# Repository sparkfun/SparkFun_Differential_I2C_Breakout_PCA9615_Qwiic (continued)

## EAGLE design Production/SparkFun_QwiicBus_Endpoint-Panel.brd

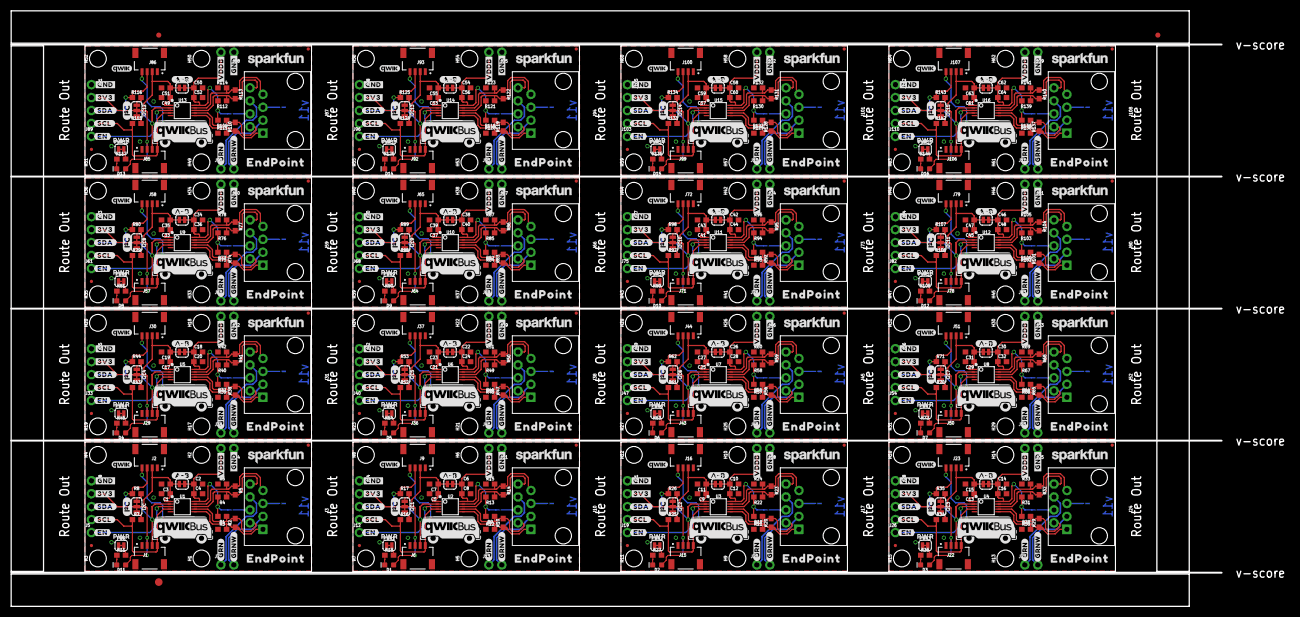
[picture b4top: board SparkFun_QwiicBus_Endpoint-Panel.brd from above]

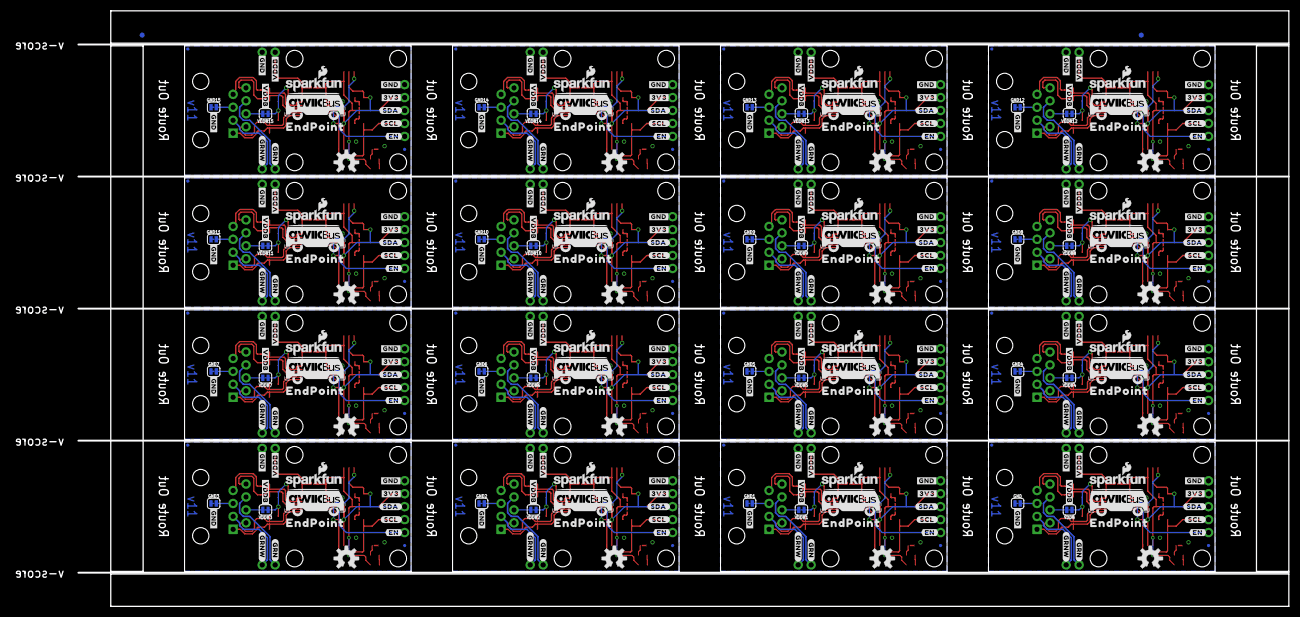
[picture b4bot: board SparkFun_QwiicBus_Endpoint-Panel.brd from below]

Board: 2 copper layers, 237.5 x 116.8 mm, 1077 parts (306 on the bottom side), 288 nets.

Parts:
A-B, A-B1, A-B2, A-B3, A-B4, A-B5, A-B6, A-B7, A-B8, A-B9, A-B10, A-B11, A-B12, A-B13, A-B14, A-B15: JUMPER; SMT-JUMPER_2_NC_TRACE_SILK
C1, C2, C5, C6, C9, C10, C13, C14, C17, C18, C21, C22, C25, C26, C29, C30, C33, C34, C37, C38, C41, C42, C45, C46, C49, C50, C53, C54, C57, C58, C61, C62: 0.1uF; 0603
C3, C4, C7, C8, C11, C12, C15, C16, C19, C20, C23, C24, C27, C28, C31, C32, C35, C36, C39, C40, C43, C44, C47, C48, C51, C52, C55, C56, C59, C60, C63, C64: 1.0uF; 0603
D1, D2, D3, D4, D5, D6, D7, D8, D9, D10, D11, D12, D13, D14, D15, D16: RED; LED-0603
E$1, E$2, E$3, E$4: FIDUCIAL-1X2
E$5: FIDUCIAL-1.5X3
FD1, FD2, FD3, FD4, FD5, FD6, FD7, FD8, FD9, FD10, FD11, FD12, FD13, FD14, FD15, FD16, FD17, FD18, FD19, FD20, FD21, FD22, FD23, FD24, FD25, FD26, FD27, FD28, FD29, FD30, FD31, FD32, FD33, FD34, FD35, FD36, FD37, FD38, FD39, FD40, FD41, FD42, FD43, FD44, FD45, FD46, FD47, FD48, FD49, FD50, FD51, FD52, FD53, FD54, FD55, FD56, FD57, FD58, FD59, FD60, FD61, FD62, FD63, FD64: FIDUCIALUFIDUCIAL; FIDUCIAL-MICRO
GND, GND1, GND2, GND3, GND4, GND5, GND6, GND7, GND8, GND9, GND10, GND11, GND12, GND13, GND14, GND15: JUMPER-SMT_2_NC_TRACE_SILK; SMT-JUMPER_2_NC_TRACE_SILK
H1, H2, H3, H4, H5, H6, H7, H8, H9, H10, H11, H12, H13, H14, H15, H16, H17, H18, H19, H20, H21, H22, H23, H24, H25, H26, H27, H28, H29, H30, H31, H32, H33, H34, H35, H36, H37, H38, H39, H40, H41, H42, H43, H44, H45, H46, H47, H48, H49, H50, H51, H52, H53, H54, H55, H56, H57, H58, H59, H60, H61, H62, H63, H64: STAND-OFF
I2C, I2C1, I2C2, I2C3, I2C4, I2C5, I2C6, I2C7, I2C8, I2C9, I2C10, I2C11, I2C12, I2C13, I2C14, I2C15: JUMPER-SMT_3_2-NC_TRACE_SILK; SMT-JUMPER_3_2-NC_TRACE_SILK
J1, J2, J6, J9, J15, J16, J22, J23, J29, J30, J36, J37, J43, J44, J50, J51, J57, J58, J64, J65, J71, J72, J78, J79, J85, J86, J92, J93, J99, J100, J106, J107: QWIIC; JST04_1MM_RA
J3, J10, J17, J24, J31, J38, J45, J52, J59, J66, J73, J80, J87, J94, J101, J108: RJ45; RJ45-8
J4, J7, J11, J13, J18, J20, J25, J27, J32, J34, J39, J41, J46, J48, J53, J55, J60, J62, J67, J69, J74, J76, J81, J83, J88, J90, J95, J97, J102, J104, J109, J111: 1X02_NO_SILK
J5, J12, J19, J26, J33, J40, J47, J54, J61, J68, J75, J82, J89, J96, J103, J110: 1X01_NO_SILK
J8, J14, J21, J28, J35, J42, J49, J56, J63, J70, J77, J84, J91, J98, J105, J112: 1X04_NO_SILK
LOGO1, LOGO6, LOGO11, LOGO16, LOGO21, LOGO26, LOGO31, LOGO36, LOGO41, LOGO46, LOGO51, LOGO56, LOGO61, LOGO66, LOGO71, LOGO76: OSHW-LOGOM; OSHW-LOGO-M
LOGO2, LOGO8, LOGO13, LOGO18, LOGO23, LOGO28, LOGO33, LOGO38, LOGO43, LOGO48, LOGO53, LOGO58, LOGO63, LOGO68, LOGO73, LOGO78: REVISION
LOGO3, LOGO9, LOGO14, LOGO19, LOGO24, LOGO29, LOGO34, LOGO39, LOGO44, LOGO49, LOGO54, LOGO59, LOGO64, LOGO69, LOGO74, LOGO79: QWIIC_LOGO_4MM; QWIIC_4MM
LOGO4, LOGO10, LOGO15, LOGO20, LOGO25, LOGO30, LOGO35, LOGO40, LOGO45, LOGO50, LOGO55, LOGO60, LOGO65, LOGO70, LOGO75, LOGO80: SFE_LOGO_NAME_FLAME.1_INCH; SFE_LOGO_NAME_FLAME_.1
LOGO5, LOGO7, LOGO12, LOGO17, LOGO22, LOGO27, LOGO32, LOGO37, LOGO42, LOGO47, LOGO52, LOGO57, LOGO62, LOGO67, LOGO72, LOGO77: SFE_LOGO_NAME.1_INCH; SFE_LOGO_NAME_.1
PWR, PWR1, PWR2, PWR3, PWR4, PWR5, PWR6, PWR7, PWR8, PWR9, PWR10, PWR11, PWR12, PWR13, PWR14, PWR15: JUMPER-SMT_2_NC_TRACE_SILK; SMT-JUMPER_2_NC_TRACE_SILK
R1, R3, R4, R6, R9, R12, R13, R15, R19, R21, R22, R24, R28, R30, R31, R33, R37, R39, R40, R42, R46, R48, R49, R51, R55, R57, R58, R60, R64, R66, R67, R69, R73, R75, R76, R78, R82, R84, R85, R87, R91, R93, R94, R96, R100, R102, R103, R105, R109, R111, R112, R114, R118, R120, R121, R123, R127, R129, R130, R132, R136, R138, R139, R141: 390; 0603
R2, R5, R10, R14, R20, R23, R29, R32, R38, R41, R47, R50, R56, R59, R65, R68, R74, R77, R83, R86, R92, R95, R101, R104, R110, R113, R119, R122, R128, R131, R137, R140: 100; 0603
R7, R8, R16, R17, R25, R26, R34, R35, R43, R44, R52, R53, R61, R62, R70, R71, R79, R80, R88, R89, R97, R98, R106, R107, R115, R116, R124, R125, R133, R134, R142, R143: 4.7k; 0603
R11, R18, R27, R36, R45, R54, R63, R72, R81, R90, R99, R108, R117, R126, R135, R144: 1k; 0603
U1, U2, U3, U4, U5, U6, U7, U8, U9, U10, U11, U12, U13, U14, U15, U16: PCA9615; TSSOP10
U$1, U$24, U$55, U$82, U$109, U$136, U$163, U$190, U$217, U$244, U$271, U$298, U$325, U$352, U$379, U$406: I2C
U$2, U$3, U$4, U$5, U$6, U$29, U$30, U$31, U$32, U$33, U$56, U$57, U$58, U$59, U$60, U$83, U$84, U$85, U$86, U$87, U$110, U$111, U$112, U$113, U$114, U$137, U$138, U$139, U$140, U$141, U$164, U$165, U$166, U$167, U$168, U$191, U$192, U$193, U$194, U$195, U$218, U$219, U$220, U$221, U$222, U$245, U$246, U$247, U$248, U$249, U$272, U$273, U$274, U$275, U$276, U$299, U$300, U$301, U$302, U$303, U$326, U$327, U$328, U$329, U$330, U$353, U$354, U$355, U$356, U$357, U$380, U$381, U$382, U$383, U$384, U$407, U$408, U$409, U$410, U$411: #GND#0
U$7, U$8, U$34, U$35, U$61, U$62, U$88, U$89, U$115, U$116, U$142, U$143, U$169, U$170, U$196, U$197, U$223, U$224, U$250, U$251, U$277, U$278, U$304, U$305, U$331, U$332, U$358, U$359, U$385, U$386, U$412, U$413: #3V3#0
U$9, U$15, U$36, U$42, U$63, U$69, U$90, U$96, U$117, U$123, U$144, U$150, U$171, U$177, U$198, U$204, U$225, U$231, U$252, U$258, U$279, U$285, U$306, U$312, U$333, U$339, U$360, U$366, U$387, U$393, U$414, U$420: #SDA#0
U$10, U$16, U$37, U$43, U$64, U$70, U$91, U$97, U$118, U$124, U$145, U$151, U$172, U$178, U$199, U$205, U$226, U$232, U$253, U$259, U$280, U$286, U$307, U$313, U$334, U$340, U$361, U$367, U$388, U$394, U$415, U$421: #SCL#0
U$11, U$17, U$38, U$44, U$65, U$71, U$92, U$98, U$119, U$125, U$146, U$152, U$173, U$179, U$200, U$206, U$227, U$233, U$254, U$260, U$281, U$287, U$308, U$314, U$335, U$341, U$362, U$368, U$389, U$395, U$416, U$422: #EN#0
U$12, U$13, U$14, U$39, U$40, U$41, U$66, U$67, U$68, U$93, U$94, U$95, U$120, U$121, U$122, U$147, U$148, U$149, U$174, U$175, U$176, U$201, U$202, U$203, U$228, U$229, U$230, U$255, U$256, U$257, U$282, U$283, U$284, U$309, U$310, U$311, U$336, U$337, U$338, U$363, U$364, U$365, U$390, U$391, U$392, U$417, U$418, U$419: #VDDB#0
U$18, U$45, U$72, U$99, U$126, U$153, U$180, U$207, U$234, U$261, U$288, U$315, U$342, U$369, U$396, U$423: #A#B#0
U$19, U$20, U$46, U$47, U$73, U$74, U$100, U$101, U$127, U$128, U$154, U$155, U$181, U$182, U$208, U$209, U$235, U$236, U$262, U$263, U$289, U$290, U$316, U$317, U$343, U$344, U$370, U$371, U$397, U$398, U$424, U$425: #GRNW#0
U$21, U$22, U$48, U$49, U$75, U$76, U$102, U$103, U$129, U$130, U$156, U$157, U$183, U$184, U$210, U$211, U$237, U$238, U$264, U$265, U$291, U$292, U$318, U$319, U$345, U$346, U$372, U$373, U$399, U$400, U$426, U$427: #GRN#0
U$23, U$28, U$53, U$54, U$80, U$81, U$107, U$108, U$134, U$135, U$161, U$162, U$188, U$189, U$215, U$216, U$242, U$243, U$269, U$270, U$296, U$297, U$323, U$324, U$350, U$351, U$377, U$378, U$404, U$405, U$431, U$432: QWIICBUS#WORKING#LOGO#JPG
U$25, U$26, U$50, U$51, U$77, U$78, U$104, U$105, U$131, U$132, U$158, U$159, U$185, U$186, U$212, U$213, U$239, U$240, U$266, U$267, U$293, U$294, U$320, U$321, U$347, U$348, U$374, U$375, U$401, U$402, U$428, U$429: ENDPOINT0
U$27, U$52, U$79, U$106, U$133, U$160, U$187, U$214, U$241, U$268, U$295, U$322, U$349, U$376, U$403, U$430: PWR0
VDDB, VDDB1, VDDB2, VDDB3, VDDB4, VDDB5, VDDB6, VDDB7, VDDB8, VDDB9, VDDB10, VDDB11, VDDB12, VDDB13, VDDB14, VDDB15: JUMPER-SMT_2_NC_TRACE_SILK; SMT-JUMPER_2_NC_TRACE_SILK

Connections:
DSCL_N: J3.1, R2.1, R3.2, U1.6
DSCL_N1: J10.1, R10.1, R12.2, U2.6
DSCL_N2: J17.1, R20.1, R21.2, U3.6
DSCL_N3: J24.1, R29.1, R30.2, U4.6
DSCL_N4: J31.1, R38.1, R39.2, U5.6
DSCL_N5: J38.1, R47.1, R48.2, U6.6
DSCL_N6: J45.1, R56.1, R57.2, U7.6
DSCL_N7: J52.1, R65.1, R66.2, U8.6
DSCL_N8: J59.1, R74.1, R75.2, U9.6
DSCL_N9: J66.1, R83.1, R84.2, U10.6
DSCL_N10: J73.1, R92.1, R93.2, U11.6
DSCL_N11: J80.1, R101.1, R102.2, U12.6
DSCL_N12: J87.1, R110.1, R111.2, U13.6
DSCL_N13: J94.1, R119.1, R120.2, U14.6
DSCL_N14: J101.1, R128.1, R129.2, U15.6
DSCL_N15: J108.1, R137.1, R138.2, U16.6
DSCL_P: J3.2, R1.1, R2.2, U1.7
DSCL_P1: J10.2, R9.1, R10.2, U2.7
DSCL_P2: J17.2, R19.1, R20.2, U3.7
DSCL_P3: J24.2, R28.1, R29.2, U4.7
DSCL_P4: J31.2, R37.1, R38.2, U5.7
DSCL_P5: J38.2, R46.1, R47.2, U6.7
DSCL_P6: J45.2, R55.1, R56.2, U7.7
DSCL_P7: J52.2, R64.1, R65.2, U8.7
DSCL_P8: J59.2, R73.1, R74.2, U9.7
DSCL_P9: J66.2, R82.1, R83.2, U10.7
DSCL_P10: J73.2, R91.1, R92.2, U11.7
DSCL_P11: J80.2, R100.1, R101.2, U12.7
DSCL_P12: J87.2, R109.1, R110.2, U13.7
DSCL_P13: J94.2, R118.1, R119.2, U14.7
DSCL_P14: J101.2, R127.1, R128.2, U15.7
DSCL_P15: J108.2, R136.1, R137.2, U16.7
DSDA_N: J3.7, R5.1, R6.2, U1.9
DSDA_N1: J10.7, R14.1, R15.2, U2.9
DSDA_N2: J17.7, R23.1, R24.2, U3.9
DSDA_N3: J24.7, R32.1, R33.2, U4.9
DSDA_N4: J31.7, R41.1, R42.2, U5.9
DSDA_N5: J38.7, R50.1, R51.2, U6.9
DSDA_N6: J45.7, R59.1, R60.2, U7.9
DSDA_N7: J52.7, R68.1, R69.2, U8.9
DSDA_N8: J59.7, R77.1, R78.2, U9.9
DSDA_N9: J66.7, R86.1, R87.2, U10.9
DSDA_N10: J73.7, R95.1, R96.2, U11.9
DSDA_N11: J80.7, R104.1, R105.2, U12.9
DSDA_N12: J87.7, R113.1, R114.2, U13.9
DSDA_N13: J94.7, R122.1, R123.2, U14.9
DSDA_N14: J101.7, R131.1, R132.2, U15.9
DSDA_N15: J108.7, R140.1, R141.2, U16.9
DSDA_P: J3.8, R4.1, R5.2, U1.8
DSDA_P1: J10.8, R13.1, R14.2, U2.8
DSDA_P2: J17.8, R22.1, R23.2, U3.8
DSDA_P3: J24.8, R31.1, R32.2, U4.8
DSDA_P4: J31.8, R40.1, R41.2, U5.8
DSDA_P5: J38.8, R49.1, R50.2, U6.8
DSDA_P6: J45.8, R58.1, R59.2, U7.8
DSDA_P7: J52.8, R67.1, R68.2, U8.8
DSDA_P8: J59.8, R76.1, R77.2, U9.8
DSDA_P9: J66.8, R85.1, R86.2, U10.8
DSDA_P10: J73.8, R94.1, R95.2, U11.8
DSDA_P11: J80.8, R103.1, R104.2, U12.8
DSDA_P12: J87.8, R112.1, R113.2, U13.8
DSDA_P13: J94.8, R121.1, R122.2, U14.8
DSDA_P14: J101.8, R130.1, R131.2, U15.8
DSDA_P15: J108.8, R139.1, R140.2, U16.8
EN: J5.1, U1.3
EN1: J12.1, U2.3
EN2: J19.1, U3.3
EN3: J26.1, U4.3
EN4: J33.1, U5.3
EN5: J40.1, U6.3
EN6: J47.1, U7.3
EN7: J54.1, U8.3
EN8: J61.1, U9.3
EN9: J68.1, U10.3
EN10: J75.1, U11.3
EN11: J82.1, U12.3
EN12: J89.1, U13.3
EN13: J96.1, U14.3
EN14: J103.1, U15.3
EN15: J110.1, U16.3
GND: C1.2, C2.2, C3.2, C4.2, GND.1, J1.1, J2.1, J4.1, J8.1, PWR.1, R3.1, R6.1, U1.5
GND1: C5.2, C6.2, C7.2, C8.2, GND1.1, J6.1, J9.1, J11.1, J14.1, PWR1.1, R12.1, R15.1, U2.5
GND2: C9.2, C10.2, C11.2, C12.2, GND2.1, J15.1, J16.1, J18.1, J21.1, PWR2.1, R21.1, R24.1, U3.5
GND3: C13.2, C14.2, C15.2, C16.2, GND3.1, J22.1, J23.1, J25.1, J28.1, PWR3.1, R30.1, R33.1, U4.5
GND4: C17.2, C18.2, C19.2, C20.2, GND4.1, J29.1, J30.1, J32.1, J35.1, PWR4.1, R39.1, R42.1, U5.5
GND5: C21.2, C22.2, C23.2, C24.2, GND5.1, J36.1, J37.1, J39.1, J42.1, PWR5.1, R48.1, R51.1, U6.5
GND6: C25.2, C26.2, C27.2, C28.2, GND6.1, J43.1, J44.1, J46.1, J49.1, PWR6.1, R57.1, R60.1, U7.5
GND7: C29.2, C30.2, C31.2, C32.2, GND7.1, J50.1, J51.1, J53.1, J56.1, PWR7.1, R66.1, R69.1, U8.5
GND8: C33.2, C34.2, C35.2, C36.2, GND8.1, J57.1, J58.1, J60.1, J63.1, PWR8.1, R75.1, R78.1, U9.5
GND9: C37.2, C38.2, C39.2, C40.2, GND9.1, J64.1, J65.1, J67.1, J70.1, PWR9.1, R84.1, R87.1, U10.5
GND10: C41.2, C42.2, C43.2, C44.2, GND10.1, J71.1, J72.1, J74.1, J77.1, PWR10.1, R93.1, R96.1, U11.5
GND11: C45.2, C46.2, C47.2, C48.2, GND11.1, J78.1, J79.1, J81.1, J84.1, PWR11.1, R102.1, R105.1, U12.5
GND12: C49.2, C50.2, C51.2, C52.2, GND12.1, J85.1, J86.1, J88.1, J91.1, PWR12.1, R111.1, R114.1, U13.5
GND13: C53.2, C54.2, C55.2, C56.2, GND13.1, J92.1, J93.1, J95.1, J98.1, PWR13.1, R120.1, R123.1, U14.5
GND14: C57.2, C58.2, C59.2, C60.2, GND14.1, J99.1, J100.1, J102.1, J105.1, PWR14.1, R129.1, R132.1, U15.5
GND15: C61.2, C62.2, C63.2, C64.2, GND15.1, J106.1, J107.1, J109.1, J112.1, PWR15.1, R138.1, R141.1, U16.5
GRN_N: J3.6, J7.1
GRN_N1: J10.6, J13.1
GRN_N2: J17.6, J20.1
GRN_N3: J24.6, J27.1
GRN_N4: J31.6, J34.1
GRN_N5: J38.6, J41.1
GRN_N6: J45.6, J48.1
GRN_N7: J52.6, J55.1
GRN_N8: J59.6, J62.1
GRN_N9: J66.6, J69.1
GRN_N10: J73.6, J76.1
GRN_N11: J80.6, J83.1
GRN_N12: J87.6, J90.1
GRN_N13: J94.6, J97.1
GRN_N14: J101.6, J104.1
GRN_N15: J108.6, J111.1
GRN_P: J3.3, J7.2
GRN_P1: J10.3, J13.2
GRN_P2: J17.3, J20.2
GRN_P3: J24.3, J27.2
GRN_P4: J31.3, J34.2
GRN_P5: J38.3, J41.2
GRN_P6: J45.3, J48.2
GRN_P7: J52.3, J55.2
GRN_P8: J59.3, J62.2
GRN_P9: J66.3, J69.2
GRN_P10: J73.3, J76.2
GRN_P11: J80.3, J83.2
GRN_P12: J87.3, J90.2
GRN_P13: J94.3, J97.2
GRN_P14: J101.3, J104.2
GRN_P15: J108.3, J111.2
unnamed: J3.4, VDDB.2
unnamed: GND.2, J3.5
unnamed: I2C.1, R8.2
unnamed: I2C.3, R7.2
unnamed: I2C1.1, R17.2
unnamed: I2C1.3, R16.2
unnamed: J10.4, VDDB1.2
unnamed: GND1.2, J10.5
unnamed: D1.C, R18.1
unnamed: PWR1.2, R18.2
unnamed: I2C2.1, R26.2
unnamed: I2C2.3, R25.2
unnamed: D11.C, R11.1
unnamed: PWR.2, R11.2
unnamed: J17.4, VDDB2.2
unnamed: GND2.2, J17.5
unnamed: D2.C, R27.1
unnamed: PWR2.2, R27.2
unnamed: I2C3.1, R35.2
unnamed: I2C3.3, R34.2
unnamed: J24.4, VDDB3.2
unnamed: GND3.2, J24.5
unnamed: D3.C, R36.1
unnamed: PWR3.2, R36.2
unnamed: I2C4.1, R44.2
unnamed: I2C4.3, R43.2
unnamed: J31.4, VDDB4.2
unnamed: GND4.2, J31.5
unnamed: D4.C, R45.1
unnamed: PWR4.2, R45.2
unnamed: I2C5.1, R53.2
unnamed: I2C5.3, R52.2
unnamed: J38.4, VDDB5.2
unnamed: GND5.2, J38.5
unnamed: D5.C, R54.1
unnamed: PWR5.2, R54.2
unnamed: I2C6.1, R62.2
unnamed: I2C6.3, R61.2
unnamed: J45.4, VDDB6.2
unnamed: GND6.2, J45.5
unnamed: D6.C, R63.1
unnamed: PWR6.2, R63.2
unnamed: I2C7.1, R71.2
unnamed: I2C7.3, R70.2
unnamed: J52.4, VDDB7.2
unnamed: GND7.2, J52.5
unnamed: D7.C, R72.1
unnamed: PWR7.2, R72.2
unnamed: I2C8.1, R80.2
unnamed: I2C8.3, R79.2
unnamed: J59.4, VDDB8.2
unnamed: GND8.2, J59.5
unnamed: D8.C, R81.1
unnamed: PWR8.2, R81.2
unnamed: I2C9.1, R89.2
unnamed: I2C9.3, R88.2
unnamed: J66.4, VDDB9.2
unnamed: GND9.2, J66.5
unnamed: D9.C, R90.1
unnamed: PWR9.2, R90.2
unnamed: I2C10.1, R98.2
unnamed: I2C10.3, R97.2
unnamed: J73.4, VDDB10.2
unnamed: GND10.2, J73.5
unnamed: D10.C, R99.1
unnamed: PWR10.2, R99.2
unnamed: I2C11.1, R107.2
unnamed: I2C11.3, R106.2
unnamed: J80.4, VDDB11.2
unnamed: GND11.2, J80.5
unnamed: D12.C, R108.1
unnamed: PWR11.2, R108.2
unnamed: I2C12.1, R116.2
unnamed: I2C12.3, R115.2
unnamed: J87.4, VDDB12.2
unnamed: GND12.2, J87.5
unnamed: D13.C, R117.1
unnamed: PWR12.2, R117.2
unnamed: I2C13.1, R125.2
unnamed: I2C13.3, R124.2
unnamed: J94.4, VDDB13.2
unnamed: GND13.2, J94.5
unnamed: D14.C, R126.1
unnamed: PWR13.2, R126.2
unnamed: I2C14.1, R134.2
unnamed: I2C14.3, R133.2
unnamed: J101.4, VDDB14.2
unnamed: GND14.2, J101.5
unnamed: D15.C, R135.1
unnamed: PWR14.2, R135.2
unnamed: I2C15.1, R143.2
unnamed: I2C15.3, R142.2
unnamed: J108.4, VDDB15.2
unnamed: GND15.2, J108.5
unnamed: D16.C, R144.1
unnamed: PWR15.2, R144.2
SCL: J1.4, J2.4, J8.4, R7.1, U1.4
SCL1: J6.4, J9.4, J14.4, R16.1, U2.4
SCL2: J15.4, J16.4, J21.4, R25.1, U3.4
SCL3: J22.4, J23.4, J28.4, R34.1, U4.4
SCL4: J29.4, J30.4, J35.4, R43.1, U5.4
SCL5: J36.4, J37.4, J42.4, R52.1, U6.4
SCL6: J43.4, J44.4, J49.4, R61.1, U7.4
SCL7: J50.4, J51.4, J56.4, R70.1, U8.4
SCL8: J57.4, J58.4, J63.4, R79.1, U9.4
SCL9: J64.4, J65.4, J70.4, R88.1, U10.4
SCL10: J71.4, J72.4, J77.4, R97.1, U11.4
SCL11: J78.4, J79.4, J84.4, R106.1, U12.4
SCL12: J85.4, J86.4, J91.4, R115.1, U13.4
SCL13: J92.4, J93.4, J98.4, R124.1, U14.4
SCL14: J99.4, J100.4, J105.4, R133.1, U15.4
SCL15: J106.4, J107.4, J112.4, R142.1, U16.4
SDA: J1.3, J2.3, J8.3, R8.1, U1.2
SDA1: J6.3, J9.3, J14.3, R17.1, U2.2
SDA2: J15.3, J16.3, J21.3, R26.1, U3.2
SDA3: J22.3, J23.3, J28.3, R35.1, U4.2
SDA4: J29.3, J30.3, J35.3, R44.1, U5.2
SDA5: J36.3, J37.3, J42.3, R53.1, U6.2
SDA6: J43.3, J44.3, J49.3, R62.1, U7.2
SDA7: J50.3, J51.3, J56.3, R71.1, U8.2
SDA8: J57.3, J58.3, J63.3, R80.1, U9.2
SDA9: J64.3, J65.3, J70.3, R89.1, U10.2
SDA10: J71.3, J72.3, J77.3, R98.1, U11.2
SDA11: J78.3, J79.3, J84.3, R107.1, U12.2
SDA12: J85.3, J86.3, J91.3, R116.1, U13.2
SDA13: J92.3, J93.3, J98.3, R125.1, U14.2
SDA14: J99.3, J100.3, J105.3, R134.1, U15.2
SDA15: J106.3, J107.3, J112.3, R143.1, U16.2
VDD_A: A-B.1, C1.1, C3.1, D11.A, I2C.2, J1.2, J2.2, J8.2, U1.1
VDD_A1: A-B1.1, C5.1, C7.1, D1.A, I2C1.2, J6.2, J9.2, J14.2, U2.1
VDD_A2: A-B2.1, C9.1, C11.1, D2.A, I2C2.2, J15.2, J16.2, J21.2, U3.1
VDD_A3: A-B3.1, C13.1, C15.1, D3.A, I2C3.2, J22.2, J23.2, J28.2, U4.1
VDD_A4: A-B4.1, C17.1, C19.1, D4.A, I2C4.2, J29.2, J30.2, J35.2, U5.1
VDD_A5: A-B5.1, C21.1, C23.1, D5.A, I2C5.2, J36.2, J37.2, J42.2, U6.1
VDD_A6: A-B6.1, C25.1, C27.1, D6.A, I2C6.2, J43.2, J44.2, J49.2, U7.1
VDD_A7: A-B7.1, C29.1, C31.1, D7.A, I2C7.2, J50.2, J51.2, J56.2, U8.1
VDD_A8: A-B8.1, C33.1, C35.1, D8.A, I2C8.2, J57.2, J58.2, J63.2, U9.1
VDD_A9: A-B9.1, C37.1, C39.1, D9.A, I2C9.2, J64.2, J65.2, J70.2, U10.1
VDD_A10: A-B10.1, C41.1, C43.1, D10.A, I2C10.2, J71.2, J72.2, J77.2, U11.1
VDD_A11: A-B11.1, C45.1, C47.1, D12.A, I2C11.2, J78.2, J79.2, J84.2, U12.1
VDD_A12: A-B12.1, C49.1, C51.1, D13.A, I2C12.2, J85.2, J86.2, J91.2, U13.1
VDD_A13: A-B13.1, C53.1, C55.1, D14.A, I2C13.2, J92.2, J93.2, J98.2, U14.1
VDD_A14: A-B14.1, C57.1, C59.1, D15.A, I2C14.2, J99.2, J100.2, J105.2, U15.1
VDD_A15: A-B15.1, C61.1, C63.1, D16.A, I2C15.2, J106.2, J107.2, J112.2, U16.1
VDD_B: A-B.2, C2.1, C4.1, J4.2, R1.2, R4.2, U1.10, VDDB.1
VDD_B1: A-B1.2, C6.1, C8.1, J11.2, R9.2, R13.2, U2.10, VDDB1.1
VDD_B2: A-B2.2, C10.1, C12.1, J18.2, R19.2, R22.2, U3.10, VDDB2.1
VDD_B3: A-B3.2, C14.1, C16.1, J25.2, R28.2, R31.2, U4.10, VDDB3.1
VDD_B4: A-B4.2, C18.1, C20.1, J32.2, R37.2, R40.2, U5.10, VDDB4.1
VDD_B5: A-B5.2, C22.1, C24.1, J39.2, R46.2, R49.2, U6.10, VDDB5.1
VDD_B6: A-B6.2, C26.1, C28.1, J46.2, R55.2, R58.2, U7.10, VDDB6.1
VDD_B7: A-B7.2, C30.1, C32.1, J53.2, R64.2, R67.2, U8.10, VDDB7.1
VDD_B8: A-B8.2, C34.1, C36.1, J60.2, R73.2, R76.2, U9.10, VDDB8.1
VDD_B9: A-B9.2, C38.1, C40.1, J67.2, R82.2, R85.2, U10.10, VDDB9.1
VDD_B10: A-B10.2, C42.1, C44.1, J74.2, R91.2, R94.2, U11.10, VDDB10.1
VDD_B11: A-B11.2, C46.1, C48.1, J81.2, R100.2, R103.2, U12.10, VDDB11.1
VDD_B12: A-B12.2, C50.1, C52.1, J88.2, R109.2, R112.2, U13.10, VDDB12.1
VDD_B13: A-B13.2, C54.1, C56.1, J95.2, R118.2, R121.2, U14.10, VDDB13.1
VDD_B14: A-B14.2, C58.1, C60.1, J102.2, R127.2, R130.2, U15.10, VDDB14.1
VDD_B15: A-B15.2, C62.1, C64.1, J109.2, R136.2, R139.2, U16.10, VDDB15.1

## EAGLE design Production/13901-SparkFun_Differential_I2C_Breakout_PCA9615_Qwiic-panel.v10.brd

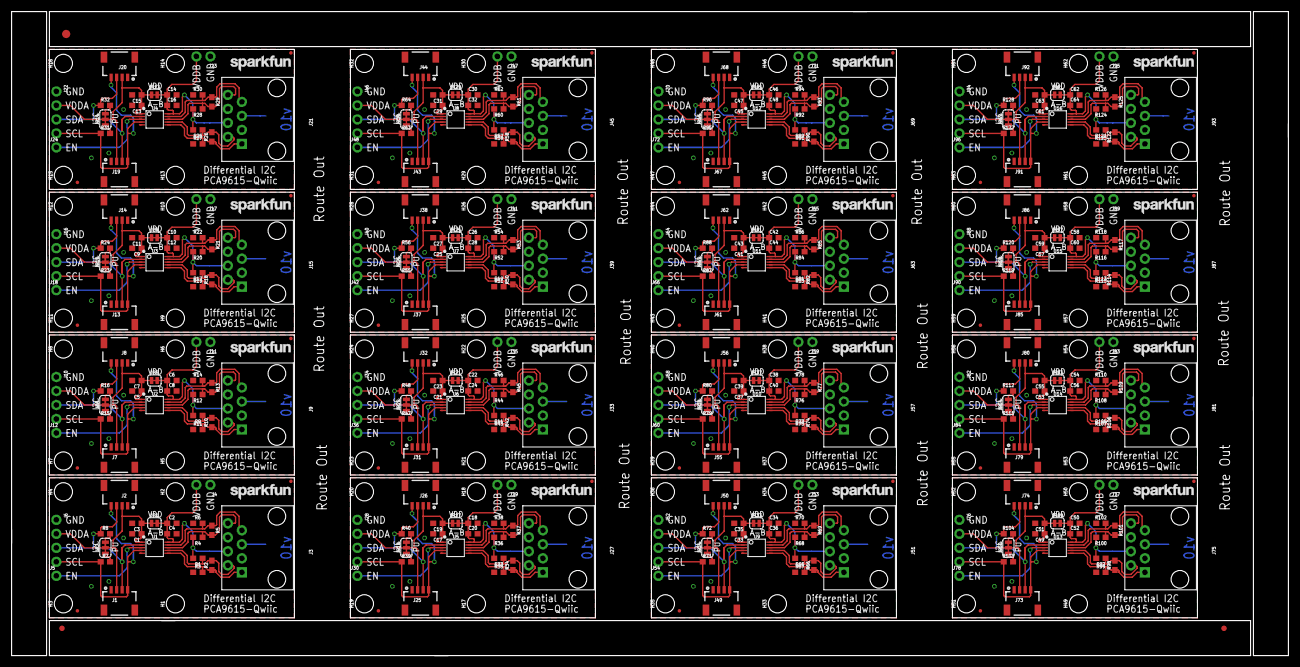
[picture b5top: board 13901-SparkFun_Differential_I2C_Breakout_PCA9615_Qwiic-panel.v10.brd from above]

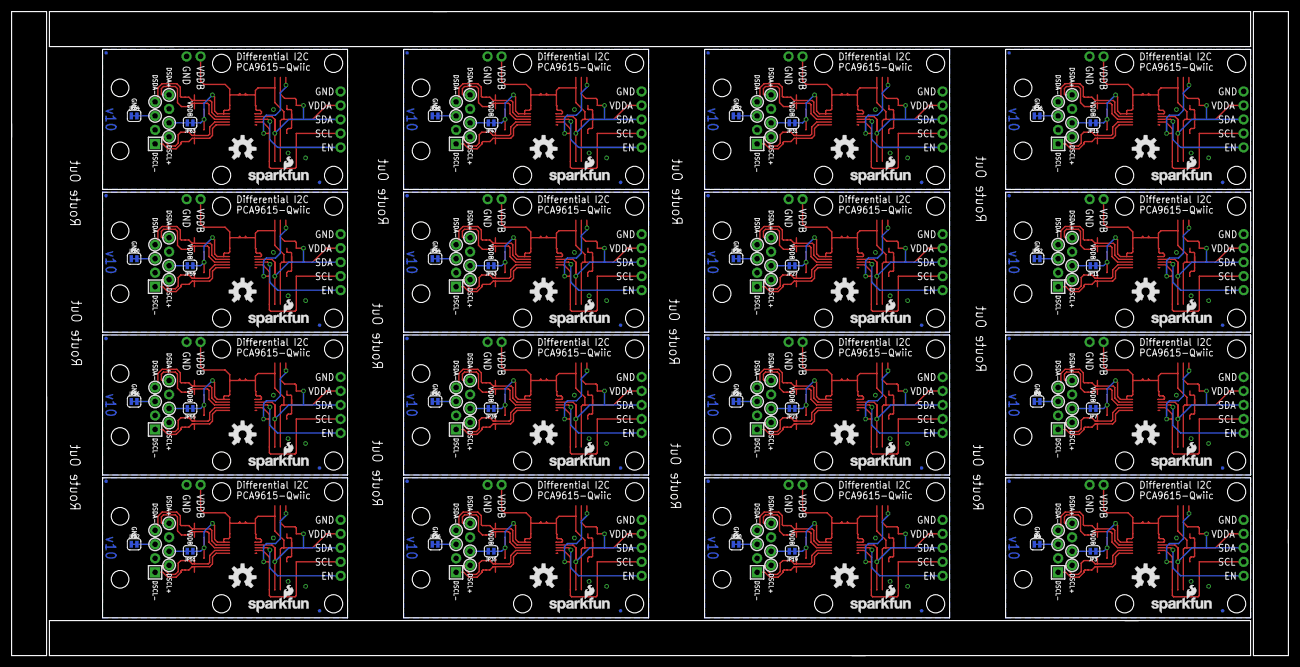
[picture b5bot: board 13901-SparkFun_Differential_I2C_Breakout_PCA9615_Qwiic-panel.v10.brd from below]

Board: 2 copper layers, 231.6 x 116.8 mm, 547 parts (96 on the bottom side), 224 nets.

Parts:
C1, C2, C5, C6, C9, C10, C13, C14, C17, C18, C21, C22, C25, C26, C29, C30, C33, C34, C37, C38, C41, C42, C45, C46, C49, C50, C53, C54, C57, C58, C61, C62: 0.1uF; 0603
C3, C4, C7, C8, C11, C12, C15, C16, C19, C20, C23, C24, C27, C28, C31, C32, C35, C36, C39, C40, C43, C44, C47, C48, C51, C52, C55, C56, C59, C60, C63, C64: 1.0uF; 0603
E$1, E$2: FIDUCIAL-1X2
E$3: FIDUCIAL-1.5X3
FD1, FD2, FD3, FD4, FD5, FD6, FD7, FD8, FD9, FD10, FD11, FD12, FD13, FD14, FD15, FD16, FD17, FD18, FD19, FD20, FD21, FD22, FD23, FD24, FD25, FD26, FD27, FD28, FD29, FD30, FD31, FD32, FD33, FD34, FD35, FD36, FD37, FD38, FD39, FD40, FD41, FD42, FD43, FD44, FD45, FD46, FD47, FD48, FD49, FD50, FD51, FD52, FD53, FD54, FD55, FD56, FD57, FD58, FD59, FD60, FD61, FD62, FD63, FD64: FIDUCIALUFIDUCIAL; FIDUCIAL-MICRO
H1, H2, H3, H4, H5, H6, H7, H8, H9, H10, H11, H12, H13, H14, H15, H16, H17, H18, H19, H20, H21, H22, H23, H24, H25, H26, H27, H28, H29, H30, H31, H32, H33, H34, H35, H36, H37, H38, H39, H40, H41, H42, H43, H44, H45, H46, H47, H48, H49, H50, H51, H52, H53, H54, H55, H56, H57, H58, H59, H60, H61, H62, H63, H64: STAND-OFF
J1, J2, J7, J8, J13, J14, J19, J20, J25, J26, J31, J32, J37, J38, J43, J44, J49, J50, J55, J56, J61, J62, J67, J68, J73, J74, J79, J80, J85, J86, J91, J92: 1X04_1MM_RA
J3, J9, J15, J21, J27, J33, J39, J45, J51, J57, J63, J69, J75, J81, J87, J93: RJ45; RJ45-8
J4, J11, J17, J23, J29, J35, J41, J47, J53, J59, J65, J71, J77, J83, J89, J95: 1X02_NO_SILK
J5, J12, J18, J24, J30, J36, J42, J48, J54, J60, J66, J72, J78, J84, J90, J96: 1X01_NO_SILK
J6, J10, J16, J22, J28, J34, J40, J46, J52, J58, J64, J70, J76, J82, J88, J94: 1X04_NO_SILK
JP1, JP5, JP9, JP13, JP17, JP21, JP25, JP29, JP33, JP37, JP41, JP45, JP49, JP53, JP57, JP61: JUMPER; SMT-JUMPER_2_NC_TRACE_SILK
JP2, JP6, JP10, JP14, JP18, JP22, JP26, JP30, JP34, JP38, JP42, JP46, JP50, JP54, JP58, JP62: SMT-JUMPER_3_2-NC_TRACE_SILK
JP3, JP4, JP7, JP8, JP11, JP12, JP15, JP16, JP19, JP20, JP23, JP24, JP27, JP28, JP31, JP32, JP35, JP36, JP39, JP40, JP43, JP44, JP47, JP48, JP51, JP52, JP55, JP56, JP59, JP60, JP63, JP64: SMT-JUMPER_2_NC_TRACE_SILK
LOGO1, LOGO2, LOGO7, LOGO10, LOGO13, LOGO16, LOGO19, LOGO22, LOGO25, LOGO28, LOGO31, LOGO34, LOGO37, LOGO40, LOGO43, LOGO46: OSHW-LOGOM; OSHW-LOGO-M
LOGO3, LOGO6, LOGO9, LOGO12, LOGO15, LOGO18, LOGO21, LOGO24, LOGO27, LOGO30, LOGO33, LOGO36, LOGO39, LOGO42, LOGO45, LOGO48: SFE_LOGO_NAME.1_INCH; SFE_LOGO_NAME_.1
LOGO4, LOGO5, LOGO8, LOGO11, LOGO14, LOGO17, LOGO20, LOGO23, LOGO26, LOGO29, LOGO32, LOGO35, LOGO38, LOGO41, LOGO44, LOGO47: SFE_LOGO_NAME_FLAME.1_INCH; SFE_LOGO_NAME_FLAME_.1
R1, R3, R4, R6, R9, R11, R12, R14, R17, R19, R20, R22, R25, R27, R28, R30, R33, R35, R36, R38, R41, R43, R44, R46, R49, R51, R52, R54, R57, R59, R60, R62, R65, R67, R68, R70, R73, R75, R76, R78, R81, R83, R84, R86, R89, R91, R92, R94, R97, R99, R100, R102, R105, R107, R108, R110, R113, R115, R116, R118, R121, R123, R124, R126: 390; 0603
R2, R5, R10, R13, R18, R21, R26, R29, R34, R37, R42, R45, R50, R53, R58, R61, R66, R69, R74, R77, R82, R85, R90, R93, R98, R101, R106, R109, R114, R117, R122, R125: 100; 0603
R7, R8, R15, R16, R23, R24, R31, R32, R39, R40, R47, R48, R55, R56, R63, R64, R71, R72, R79, R80, R87, R88, R95, R96, R103, R104, R111, R112, R119, R120, R127, R128: 4.7k; 0603
U1, U2, U3, U4, U5, U6, U7, U8, U9, U10, U11, U12, U13, U14, U15, U16: PCA9615; TSSOP10

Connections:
DSCL+: J3.2, R1.1, R2.2, U1.7
DSCL+1: J9.2, R9.1, R10.2, U2.7
DSCL+2: J15.2, R17.1, R18.2, U3.7
DSCL+3: J21.2, R25.1, R26.2, U4.7
DSCL+4: J27.2, R33.1, R34.2, U5.7
DSCL+5: J33.2, R41.1, R42.2, U6.7
DSCL+6: J39.2, R49.1, R50.2, U7.7
DSCL+7: J45.2, R57.1, R58.2, U8.7
DSCL+8: J51.2, R65.1, R66.2, U9.7
DSCL+9: J57.2, R73.1, R74.2, U10.7
DSCL+10: J63.2, R81.1, R82.2, U11.7
DSCL+11: J69.2, R89.1, R90.2, U12.7
DSCL+12: J75.2, R97.1, R98.2, U13.7
DSCL+13: J81.2, R105.1, R106.2, U14.7
DSCL+14: J87.2, R113.1, R114.2, U15.7
DSCL+15: J93.2, R121.1, R122.2, U16.7
DSCL-: J3.1, R2.1, R3.2, U1.6
DSCL-1: J9.1, R10.1, R11.2, U2.6
DSCL-2: J15.1, R18.1, R19.2, U3.6
DSCL-3: J21.1, R26.1, R27.2, U4.6
DSCL-4: J27.1, R34.1, R35.2, U5.6
DSCL-5: J33.1, R42.1, R43.2, U6.6
DSCL-6: J39.1, R50.1, R51.2, U7.6
DSCL-7: J45.1, R58.1, R59.2, U8.6
DSCL-8: J51.1, R66.1, R67.2, U9.6
DSCL-9: J57.1, R74.1, R75.2, U10.6
DSCL-10: J63.1, R82.1, R83.2, U11.6
DSCL-11: J69.1, R90.1, R91.2, U12.6
DSCL-12: J75.1, R98.1, R99.2, U13.6
DSCL-13: J81.1, R106.1, R107.2, U14.6
DSCL-14: J87.1, R114.1, R115.2, U15.6
DSCL-15: J93.1, R122.1, R123.2, U16.6
DSDA+: J3.8, R4.1, R5.2, U1.8
DSDA+1: J9.8, R12.1, R13.2, U2.8
DSDA+2: J15.8, R20.1, R21.2, U3.8
DSDA+3: J21.8, R28.1, R29.2, U4.8
DSDA+4: J27.8, R36.1, R37.2, U5.8
DSDA+5: J33.8, R44.1, R45.2, U6.8
DSDA+6: J39.8, R52.1, R53.2, U7.8
DSDA+7: J45.8, R60.1, R61.2, U8.8
DSDA+8: J51.8, R68.1, R69.2, U9.8
DSDA+9: J57.8, R76.1, R77.2, U10.8
DSDA+10: J63.8, R84.1, R85.2, U11.8
DSDA+11: J69.8, R92.1, R93.2, U12.8
DSDA+12: J75.8, R100.1, R101.2, U13.8
DSDA+13: J81.8, R108.1, R109.2, U14.8
DSDA+14: J87.8, R116.1, R117.2, U15.8
DSDA+15: J93.8, R124.1, R125.2, U16.8
DSDA-: J3.7, R5.1, R6.2, U1.9
DSDA-1: J9.7, R13.1, R14.2, U2.9
DSDA-2: J15.7, R21.1, R22.2, U3.9
DSDA-3: J21.7, R29.1, R30.2, U4.9
DSDA-4: J27.7, R37.1, R38.2, U5.9
DSDA-5: J33.7, R45.1, R46.2, U6.9
DSDA-6: J39.7, R53.1, R54.2, U7.9
DSDA-7: J45.7, R61.1, R62.2, U8.9
DSDA-8: J51.7, R69.1, R70.2, U9.9
DSDA-9: J57.7, R77.1, R78.2, U10.9
DSDA-10: J63.7, R85.1, R86.2, U11.9
DSDA-11: J69.7, R93.1, R94.2, U12.9
DSDA-12: J75.7, R101.1, R102.2, U13.9
DSDA-13: J81.7, R109.1, R110.2, U14.9
DSDA-14: J87.7, R117.1, R118.2, U15.9
DSDA-15: J93.7, R125.1, R126.2, U16.9
EN: J5.1, U1.3
EN1: J12.1, U2.3
EN2: J18.1, U3.3
EN3: J24.1, U4.3
EN4: J30.1, U5.3
EN5: J36.1, U6.3
EN6: J42.1, U7.3
EN7: J48.1, U8.3
EN8: J54.1, U9.3
EN9: J60.1, U10.3
EN10: J66.1, U11.3
EN11: J72.1, U12.3
EN12: J78.1, U13.3
EN13: J84.1, U14.3
EN14: J90.1, U15.3
EN15: J96.1, U16.3
GND: C1.2, C2.2, C3.2, C4.2, J1.1, J2.1, J4.1, J6.1, JP4.1, R3.1, R6.1, U1.5
GND1: C5.2, C6.2, C7.2, C8.2, J7.1, J8.1, J10.1, J11.1, JP8.1, R11.1, R14.1, U2.5
GND2: C9.2, C10.2, C11.2, C12.2, J13.1, J14.1, J16.1, J17.1, JP12.1, R19.1, R22.1, U3.5
GND3: C13.2, C14.2, C15.2, C16.2, J19.1, J20.1, J22.1, J23.1, JP16.1, R27.1, R30.1, U4.5
GND4: C17.2, C18.2, C19.2, C20.2, J25.1, J26.1, J28.1, J29.1, JP20.1, R35.1, R38.1, U5.5
GND5: C21.2, C22.2, C23.2, C24.2, J31.1, J32.1, J34.1, J35.1, JP24.1, R43.1, R46.1, U6.5
GND6: C25.2, C26.2, C27.2, C28.2, J37.1, J38.1, J40.1, J41.1, JP28.1, R51.1, R54.1, U7.5
GND7: C29.2, C30.2, C31.2, C32.2, J43.1, J44.1, J46.1, J47.1, JP32.1, R59.1, R62.1, U8.5
GND8: C33.2, C34.2, C35.2, C36.2, J49.1, J50.1, J52.1, J53.1, JP36.1, R67.1, R70.1, U9.5
GND9: C37.2, C38.2, C39.2, C40.2, J55.1, J56.1, J58.1, J59.1, JP40.1, R75.1, R78.1, U10.5
GND10: C41.2, C42.2, C43.2, C44.2, J61.1, J62.1, J64.1, J65.1, JP44.1, R83.1, R86.1, U11.5
GND11: C45.2, C46.2, C47.2, C48.2, J67.1, J68.1, J70.1, J71.1, JP48.1, R91.1, R94.1, U12.5
GND12: C49.2, C50.2, C51.2, C52.2, J73.1, J74.1, J76.1, J77.1, JP52.1, R99.1, R102.1, U13.5
GND13: C53.2, C54.2, C55.2, C56.2, J79.1, J80.1, J82.1, J83.1, JP56.1, R107.1, R110.1, U14.5
GND14: C57.2, C58.2, C59.2, C60.2, J85.1, J86.1, J88.1, J89.1, JP60.1, R115.1, R118.1, U15.5
GND15: C61.2, C62.2, C63.2, C64.2, J91.1, J92.1, J94.1, J95.1, JP64.1, R123.1, R126.1, U16.5
unnamed: J3.4, JP3.2
unnamed: J3.5, JP4.2
unnamed: JP2.1, R8.2
unnamed: JP2.3, R7.2
unnamed: JP6.1, R16.2
unnamed: JP6.3, R15.2
unnamed: J9.4, JP7.2
unnamed: J9.5, JP8.2
unnamed: JP10.1, R24.2
unnamed: JP10.3, R23.2
unnamed: J15.4, JP11.2
unnamed: J15.5, JP12.2
unnamed: JP14.1, R32.2
unnamed: JP14.3, R31.2
unnamed: J21.4, JP15.2
unnamed: J21.5, JP16.2
unnamed: JP18.1, R40.2
unnamed: JP18.3, R39.2
unnamed: J27.4, JP19.2
unnamed: J27.5, JP20.2
unnamed: JP22.1, R48.2
unnamed: JP22.3, R47.2
unnamed: J33.4, JP23.2
unnamed: J33.5, JP24.2
unnamed: JP26.1, R56.2
unnamed: JP26.3, R55.2
unnamed: J39.4, JP27.2
unnamed: J39.5, JP28.2
unnamed: JP30.1, R64.2
unnamed: JP30.3, R63.2
unnamed: J45.4, JP31.2
unnamed: J45.5, JP32.2
unnamed: JP34.1, R72.2
unnamed: JP34.3, R71.2
unnamed: J51.4, JP35.2
unnamed: J51.5, JP36.2
unnamed: JP38.1, R80.2
unnamed: JP38.3, R79.2
unnamed: J57.4, JP39.2
unnamed: J57.5, JP40.2
unnamed: JP42.1, R88.2
unnamed: JP42.3, R87.2
unnamed: J63.4, JP43.2
unnamed: J63.5, JP44.2
unnamed: JP46.1, R96.2
unnamed: JP46.3, R95.2
unnamed: J69.4, JP47.2
unnamed: J69.5, JP48.2
unnamed: JP50.1, R104.2
unnamed: JP50.3, R103.2
unnamed: J75.4, JP51.2
unnamed: J75.5, JP52.2
unnamed: JP54.1, R112.2
unnamed: JP54.3, R111.2
unnamed: J81.4, JP55.2
unnamed: J81.5, JP56.2
unnamed: JP58.1, R120.2
unnamed: JP58.3, R119.2
unnamed: J87.4, JP59.2
unnamed: J87.5, JP60.2
unnamed: JP62.1, R128.2
unnamed: JP62.3, R127.2
unnamed: J93.4, JP63.2
unnamed: J93.5, JP64.2
SCL: J1.4, J2.4, J6.4, R7.1, U1.4
SCL1: J7.4, J8.4, J10.4, R15.1, U2.4
SCL2: J13.4, J14.4, J16.4, R23.1, U3.4
SCL3: J19.4, J20.4, J22.4, R31.1, U4.4
SCL4: J25.4, J26.4, J28.4, R39.1, U5.4
SCL5: J31.4, J32.4, J34.4, R47.1, U6.4
SCL6: J37.4, J38.4, J40.4, R55.1, U7.4
SCL7: J43.4, J44.4, J46.4, R63.1, U8.4
SCL8: J49.4, J50.4, J52.4, R71.1, U9.4
SCL9: J55.4, J56.4, J58.4, R79.1, U10.4
SCL10: J61.4, J62.4, J64.4, R87.1, U11.4
SCL11: J67.4, J68.4, J70.4, R95.1, U12.4
SCL12: J73.4, J74.4, J76.4, R103.1, U13.4
SCL13: J79.4, J80.4, J82.4, R111.1, U14.4
SCL14: J85.4, J86.4, J88.4, R119.1, U15.4
SCL15: J91.4, J92.4, J94.4, R127.1, U16.4
SDA: J1.3, J2.3, J6.3, R8.1, U1.2
SDA1: J7.3, J8.3, J10.3, R16.1, U2.2
SDA2: J13.3, J14.3, J16.3, R24.1, U3.2
SDA3: J19.3, J20.3, J22.3, R32.1, U4.2
SDA4: J25.3, J26.3, J28.3, R40.1, U5.2
SDA5: J31.3, J32.3, J34.3, R48.1, U6.2
SDA6: J37.3, J38.3, J40.3, R56.1, U7.2
SDA7: J43.3, J44.3, J46.3, R64.1, U8.2
SDA8: J49.3, J50.3, J52.3, R72.1, U9.2
SDA9: J55.3, J56.3, J58.3, R80.1, U10.2
SDA10: J61.3, J62.3, J64.3, R88.1, U11.2
SDA11: J67.3, J68.3, J70.3, R96.1, U12.2
SDA12: J73.3, J74.3, J76.3, R104.1, U13.2
SDA13: J79.3, J80.3, J82.3, R112.1, U14.2
SDA14: J85.3, J86.3, J88.3, R120.1, U15.2
SDA15: J91.3, J92.3, J94.3, R128.1, U16.2
VDD_A: C1.1, C3.1, J1.2, J2.2, J6.2, JP1.1, JP2.2, U1.1
VDD_A1: C5.1, C7.1, J7.2, J8.2, J10.2, JP5.1, JP6.2, U2.1
VDD_A2: C9.1, C11.1, J13.2, J14.2, J16.2, JP9.1, JP10.2, U3.1
VDD_A3: C13.1, C15.1, J19.2, J20.2, J22.2, JP13.1, JP14.2, U4.1
VDD_A4: C17.1, C19.1, J25.2, J26.2, J28.2, JP17.1, JP18.2, U5.1
VDD_A5: C21.1, C23.1, J31.2, J32.2, J34.2, JP21.1, JP22.2, U6.1
VDD_A6: C25.1, C27.1, J37.2, J38.2, J40.2, JP25.1, JP26.2, U7.1
VDD_A7: C29.1, C31.1, J43.2, J44.2, J46.2, JP29.1, JP30.2, U8.1
VDD_A8: C33.1, C35.1, J49.2, J50.2, J52.2, JP33.1, JP34.2, U9.1
VDD_A9: C37.1, C39.1, J55.2, J56.2, J58.2, JP37.1, JP38.2, U10.1
VDD_A10: C41.1, C43.1, J61.2, J62.2, J64.2, JP41.1, JP42.2, U11.1
VDD_A11: C45.1, C47.1, J67.2, J68.2, J70.2, JP45.1, JP46.2, U12.1
VDD_A12: C49.1, C51.1, J73.2, J74.2, J76.2, JP49.1, JP50.2, U13.1
VDD_A13: C53.1, C55.1, J79.2, J80.2, J82.2, JP53.1, JP54.2, U14.1
VDD_A14: C57.1, C59.1, J85.2, J86.2, J88.2, JP57.1, JP58.2, U15.1
VDD_A15: C61.1, C63.1, J91.2, J92.2, J94.2, JP61.1, JP62.2, U16.1
VDD_B: C2.1, C4.1, J4.2, JP1.2, JP3.1, R1.2, R4.2, U1.10
VDD_B1: C6.1, C8.1, J11.2, JP5.2, JP7.1, R9.2, R12.2, U2.10
VDD_B2: C10.1, C12.1, J17.2, JP9.2, JP11.1, R17.2, R20.2, U3.10
VDD_B3: C14.1, C16.1, J23.2, JP13.2, JP15.1, R25.2, R28.2, U4.10
VDD_B4: C18.1, C20.1, J29.2, JP17.2, JP19.1, R33.2, R36.2, U5.10
VDD_B5: C22.1, C24.1, J35.2, JP21.2, JP23.1, R41.2, R44.2, U6.10
VDD_B6: C26.1, C28.1, J41.2, JP25.2, JP27.1, R49.2, R52.2, U7.10
VDD_B7: C30.1, C32.1, J47.2, JP29.2, JP31.1, R57.2, R60.2, U8.10
VDD_B8: C34.1, C36.1, J53.2, JP33.2, JP35.1, R65.2, R68.2, U9.10
VDD_B9: C38.1, C40.1, J59.2, JP37.2, JP39.1, R73.2, R76.2, U10.10
VDD_B10: C42.1, C44.1, J65.2, JP41.2, JP43.1, R81.2, R84.2, U11.10
VDD_B11: C46.1, C48.1, J71.2, JP45.2, JP47.1, R89.2, R92.2, U12.10
VDD_B12: C50.1, C52.1, J77.2, JP49.2, JP51.1, R97.2, R100.2, U13.10
VDD_B13: C54.1, C56.1, J83.2, JP53.2, JP55.1, R105.2, R108.2, U14.10
VDD_B14: C58.1, C60.1, J89.2, JP57.2, JP59.1, R113.2, R116.2, U15.10
VDD_B15: C62.1, C64.1, J95.2, JP61.2, JP63.1, R121.2, R124.2, U16.10

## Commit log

2017-12-07 Initial commit of .brd and .sch files
2017-12-11 Updated routing for Differential signals
2017-12-13 ENG Checklist update
    Changes made after design review and ENG checklist.
2017-12-19 Adding minor changes from QC checklist
2018-01-23 Pushing design before Redboard Review
2018-01-24 Adding PCA9615 to SFE Eagle Library
2018-01-25 ENG Design Checklist changes
2018-01-25 Ready for REDs
2018-02-01 panel
2020-07-24 making initial v11 changes
2020-07-28 post design review and checklist changes
2020-07-29 qc double check changes
2020-07-29 adding qwiicBus silk
2020-07-30 adding panel
2020-07-30 moving qwiicBus up a tad
2020-08-05 thickening VDDB trace
2020-08-19 changing labels on grn pair, removing vddb
2020-08-21 making everything 3v3
2020-08-24 removing blue pair access
2020-10-19 post FarmHand Review
2020-10-20 post checklist changes
2020-10-22 updating silk as per double check
